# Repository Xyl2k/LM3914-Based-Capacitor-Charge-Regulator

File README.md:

LM3914-Based-Capacitor-Charge-Regulator
=======================================

Schematic and board layout for the LM3914 based capacitor charge regulator
Original circuit by: HV Discharge http://www.hvdischarge.co.uk/gallery/schematics/capacitor-charge-regulator/
I just reproduced his huge 22MB bitmap (wtf man) on Eagle, may that can be useful to someone.

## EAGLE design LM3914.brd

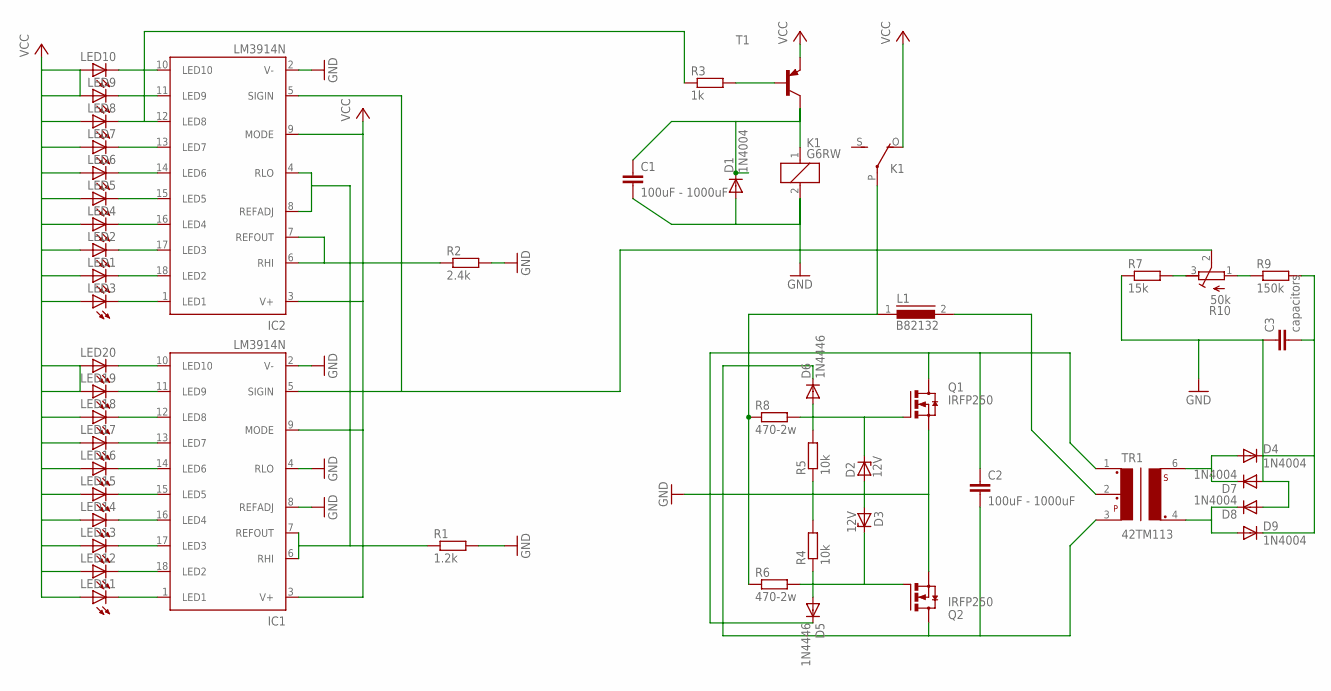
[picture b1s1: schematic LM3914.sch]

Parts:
C1, C2: 100uF - 1000uF; C2.5-3
C3: capacitors; C37.5B20
D1, D4, D7, D8, D9: 1N4004; DO41-10
D2, D3: 12V; C1702-15
D5, D6: 1N4446; DO35-10
IC1, IC2: LM3914N; DIL18
K1: G6RW
L1: B82132; SUKW2-22
LED1, LED2, LED3, LED4, LED5, LED6, LED7, LED8, LED9, LED10, LED11, LED12, LED13, LED14, LED15, LED16, LED17, LED18, LED19, LED20: LED_ELD260; LED_LD260
Q1, Q2: IRFP250; TO-247AD-V
R1: 1.2k; 0207/10
R2: 2.4k; 0207/10
R3: 1k; 0207/10
R4, R5: 10k; 0207/10
R6, R8: 470-2w; RDH/15
R7: 15k; 0207/10
R9: 150k; 0207/10
R10: 50k; RTRIM64X
T1: -PNP-TO220V; TO220V
TR1: 42TM113; 42TM

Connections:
GND: C1.2, C3.1, D1.A, D2.A, D3.A, D7.A, D8.A, IC1.2 (V-), IC1.4 (RLO), IC1.8 (REFADJ), IC2.2 (V-), K1.2, Q1.S, Q2.S, R1.2, R2.2, R4.2, R5.1, R7.1
unnamed: IC2.1 (LED1), LED3.K (C)
unnamed: IC2.18 (LED2), LED1.K (C)
unnamed: IC2.17 (LED3), LED2.K (C)
unnamed: IC2.16 (LED4), LED4.K (C)
unnamed: IC2.15 (LED5), LED5.K (C)
unnamed: IC2.14 (LED6), LED6.K (C)
unnamed: C2.1, D5.C, Q1.D, TR1.1
unnamed: IC2.12 (LED8), LED8.K (C), R3.1
unnamed: IC2.11 (LED9), LED9.K (C)
unnamed: IC2.10 (LED10), LED10.K (C)
unnamed: IC1.5 (SIGIN), IC2.5 (SIGIN), R10.2 (S)
unnamed: IC1.1 (LED1), LED11.K (C)
unnamed: IC1.18 (LED2), LED12.K (C)
unnamed: IC1.17 (LED3), LED13.K (C)
unnamed: IC1.16 (LED4), LED14.K (C)
unnamed: IC1.15 (LED5), LED15.K (C)
unnamed: IC1.14 (LED6), LED16.K (C)
unnamed: IC1.13 (LED7), LED17.K (C)
unnamed: IC1.12 (LED8), LED18.K (C)
unnamed: IC1.11 (LED9), LED19.K (C)
unnamed: IC1.10 (LED10), LED20.K (C)
unnamed: IC1.6 (RHI), IC1.7 (REFOUT), IC2.4 (RLO), IC2.8 (REFADJ), R1.1
unnamed: C1.1, D1.C, K1.1, T1.2 (C)
unnamed: IC2.6 (RHI), IC2.7 (REFOUT), R2.1
unnamed: R3.2, T1.1 (B)
unnamed: C2.2, D6.C, Q2.D, TR1.3
unnamed: IC2.13 (LED7), LED7.K (C)
unnamed: D3.C, D5.A, Q2.G, R4.1, R6.2
unnamed: D2.C, D6.A, Q1.G, R5.2, R8.2
unnamed: K1.P, L1.1, R6.1, R8.1
unnamed: L1.2, TR1.2
unnamed: D4.A, D7.C, TR1.6
unnamed: D8.C, D9.A, TR1.4
unnamed: C3.2, D4.C, D9.C, R9.2
unnamed: R9.1, R10.1 (A)
unnamed: R7.2, R10.3 (E)
VCC: IC1.3 (V+), IC1.9 (MODE), IC2.3 (V+), IC2.9 (MODE), K1.O, LED1.A, LED2.A, LED3.A, LED4.A, LED5.A, LED6.A, LED7.A, LED8.A, LED9.A, LED10.A, LED11.A, LED12.A, LED13.A, LED14.A, LED15.A, LED16.A, LED17.A, LED18.A, LED19.A, LED20.A, T1.3 (E)

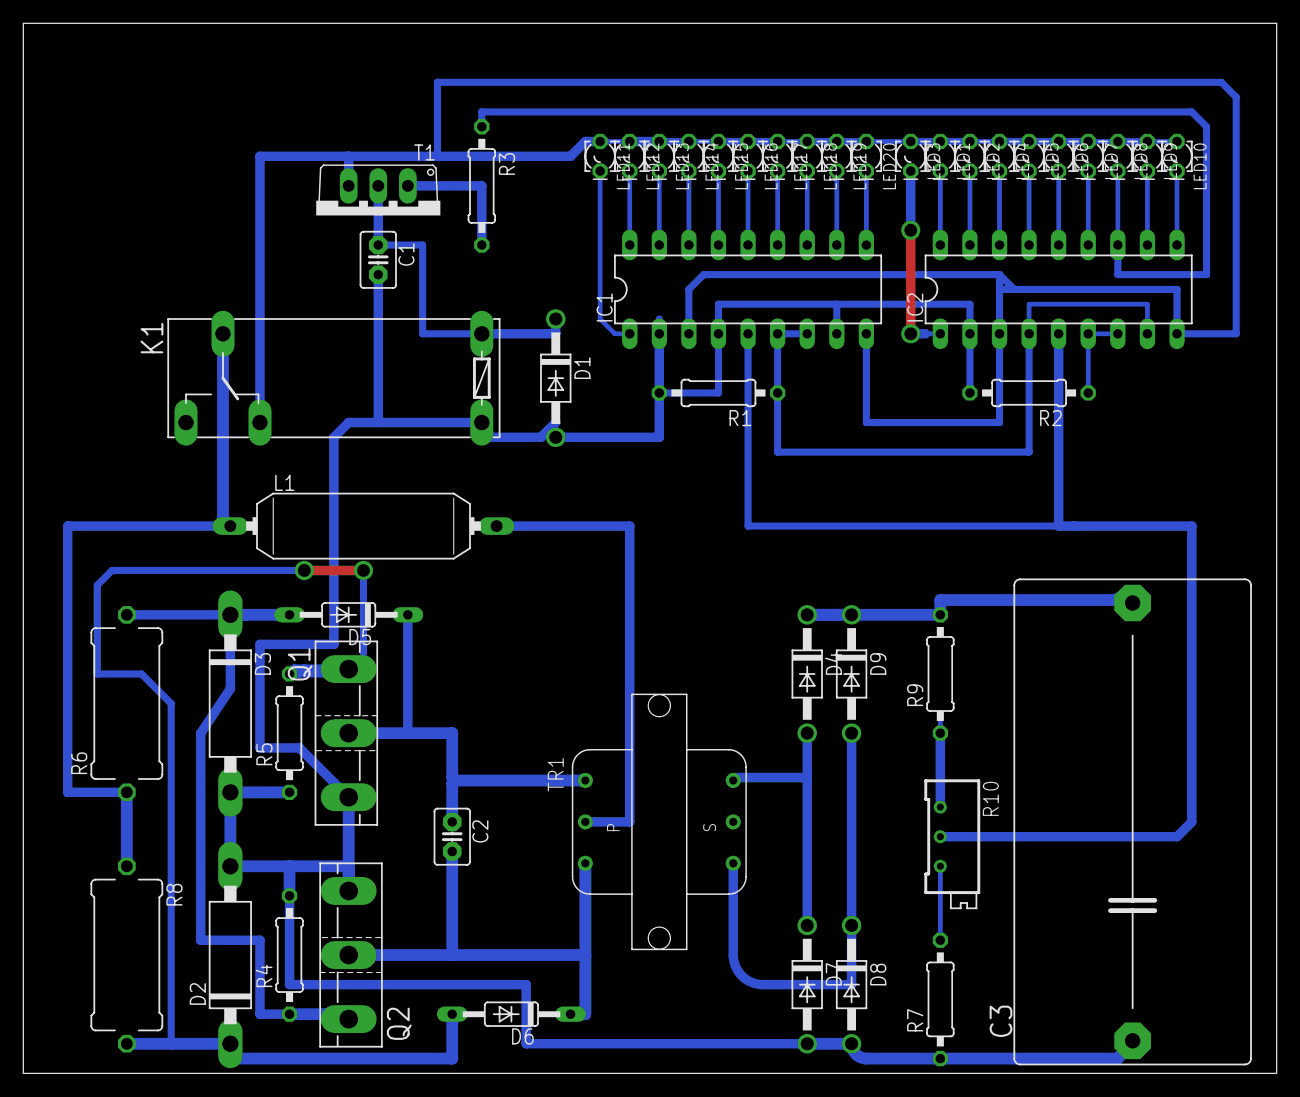
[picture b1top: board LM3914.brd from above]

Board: 2 copper layers, 107.6 x 90.2 mm, 50 parts (0 on the bottom side), 38 nets.

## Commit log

2014-12-11 :neckbeard: Added .gitattributes & .gitignore files
2014-12-11 1.0
    1.0
